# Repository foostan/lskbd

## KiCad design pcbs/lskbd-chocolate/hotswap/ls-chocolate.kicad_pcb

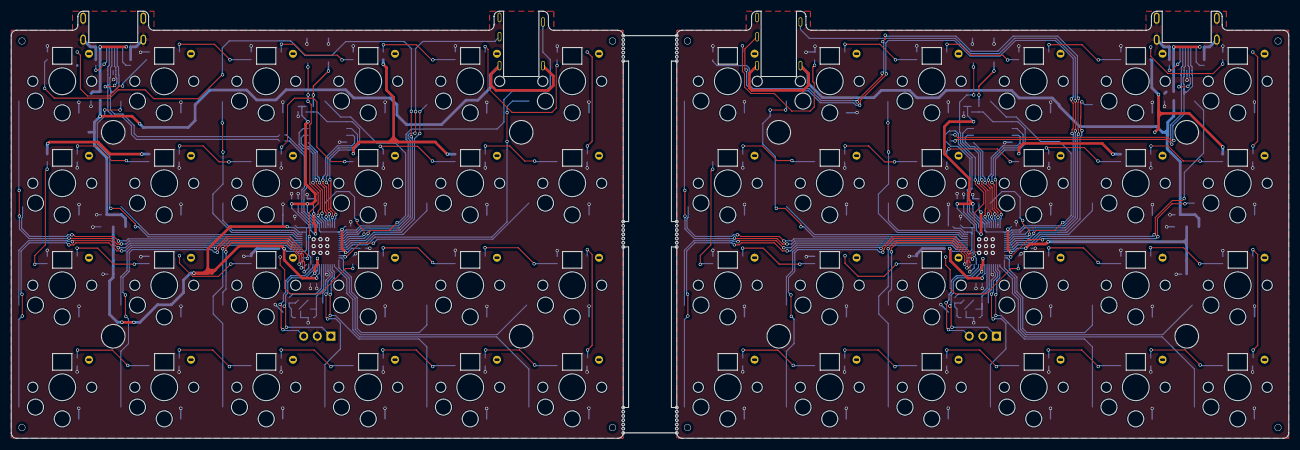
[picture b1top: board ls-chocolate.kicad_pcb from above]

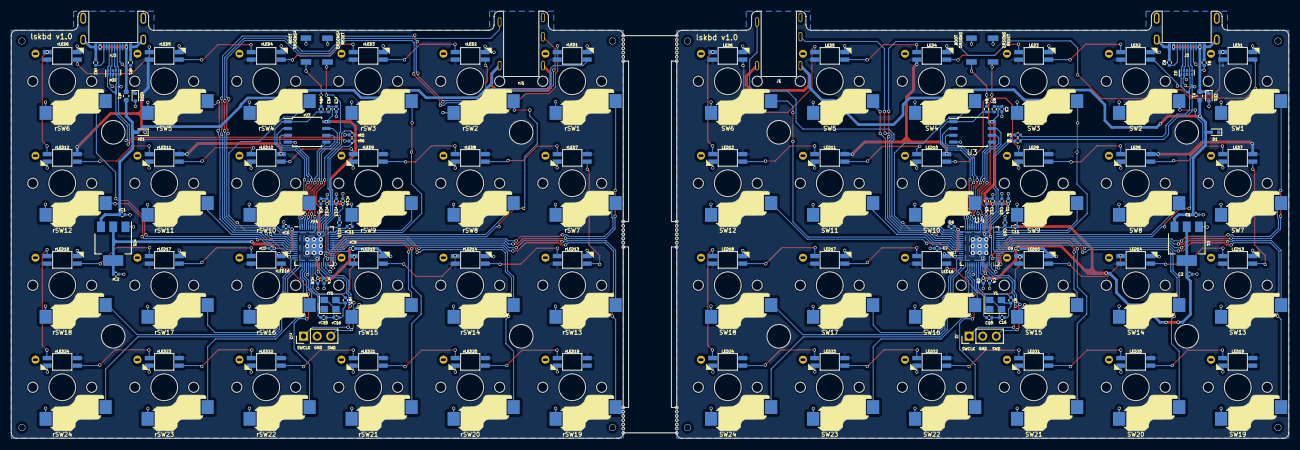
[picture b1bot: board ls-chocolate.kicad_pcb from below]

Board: 2 copper layers, 238.6 x 79.8 mm, 174 parts (168 on the bottom side), 150 nets.

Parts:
BT1, BT2, BT3: Breakaway Tabs; Breakaway_Tabs
C1, C2: 10u; C_0402_1005Metric
C3, C13, C14: 1u; C_0402_1005Metric
C4, C5, C6, C7, C8, C9, C10, C11, C12: 100n; C_0402_1005Metric
C15, C16: 27p; C_0402_1005Metric
D1: 1N4148WT; D_SOD-523
F1: BSMD0603-050-12V; Fuse_0603_1608Metric
J1: ST-0277D00-052-142
J2: Conn_01x03; PinHeader_1x03_P2.54mm_Vertical
J3: TYPE-C-31-M-13C
LED1, LED2, LED3, LED4, LED5, LED6, LED7, LED8, LED9, LED10, LED11, LED12, LED13, LED14, LED15, LED16, LED17, LED18, LED19, LED20, LED21, LED22, LED23, LED24: YS-SK6812MINI-E
R1, R2: 5.1k; R_0402_1005Metric
R3: 10k; R_0402_1005Metric
R4, R7: 1k; R_0402_1005Metric
R5, R6: 27; R_0402_1005Metric
SMDSW1, SMDSW2: TS-1088R-02026
SW1, SW2, SW3, SW4, SW5, SW6, SW7, SW8, SW9, SW10, SW11, SW12, SW13, SW14, SW15, SW16, SW17, SW18, SW19, SW20, SW21, SW22, SW23, SW24: SW_Push; keyswitch_choc12_hotswap_1u
U1: NCP1117LPST33T3G; SOT-223-3_TabPin2
U2: TPD4E05U06DQAR; USON-10_2.5x1.0mm_P0.5mm
U3: W25Q128JVSIQ; SOIC-8_5.23x5.23mm_P1.27mm
U4: RP2040; QFN-56-1EP_7x7mm_P0.4mm_EP3.2x3.2mm
Y1: 12MHz 18pF; Crystal_SMD_3225-4Pin_3.2x2.5mm
ZD1: ESD5Z5V0C; D_SOD-523
rBT1, rBT2, rBT3: Breakaway Tabs; Breakaway_Tabs
rC1, rC2: 10u; C_0402_1005Metric
rC3, rC13, rC14: 1u; C_0402_1005Metric
rC4, rC5, rC6, rC7, rC8, rC9, rC10, rC11, rC12: 100n; C_0402_1005Metric
rC15, rC16: 27p; C_0402_1005Metric
rD1: 1N4148WT; D_SOD-523
rF1: BSMD0603-050-12V; Fuse_0603_1608Metric
rJ1: ST-0277D00-052-142
rJ2: Conn_01x03; PinHeader_1x03_P2.54mm_Vertical
rJ3: TYPE-C-31-M-13C
rLED1, rLED2, rLED3, rLED4, rLED5, rLED6, rLED7, rLED8, rLED9, rLED10, rLED11, rLED12, rLED13, rLED14, rLED15, rLED16, rLED17, rLED18, rLED19, rLED20, rLED21, rLED22, rLED23, rLED24: YS-SK6812MINI-E
rR1, rR2: 5.1k; R_0402_1005Metric
rR3: 10k; R_0402_1005Metric
rR4, rR7: 1k; R_0402_1005Metric
rR5, rR6: 27; R_0402_1005Metric
rSMDSW1, rSMDSW2: TS-1088R-02026
rSW1, rSW2, rSW3, rSW4, rSW5, rSW6, rSW7, rSW8, rSW9, rSW10, rSW11, rSW12, rSW13, rSW14, rSW15, rSW16, rSW17, rSW18, rSW19, rSW20, rSW21, rSW22, rSW23, rSW24: SW_Push; keyswitch_choc12_hotswap_1u
rU1: NCP1117LPST33T3G; SOT-223-3_TabPin2
rU2: TPD4E05U06DQAR; USON-10_2.5x1.0mm_P0.5mm
rU3: W25Q128JVSIQ; SOIC-8_5.23x5.23mm_P1.27mm
rU4: RP2040; QFN-56-1EP_7x7mm_P0.4mm_EP3.2x3.2mm
rY1: 12MHz 18pF; Crystal_SMD_3225-4Pin_3.2x2.5mm
rZD1: ESD5Z5V0C; D_SOD-523

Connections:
+1V1: C4.1, C5.1, C13.1, U4.23 (DVDD), U4.45 (VREG_VOUT), U4.50 (DVDD)
+1V1R: rC4.1, rC5.1, rC13.1, rU4.23 (DVDD), rU4.45 (VREG_VOUT), rU4.50 (DVDD)
+3V3: C2.1, C3.1, C6.1, C7.1, C8.1, C9.1, C10.1, C11.1, C12.1, C14.1, R3.2, U1.2 (VO), U3.8 (VCC), U4.1 (IOVDD), U4.10 (IOVDD), U4.22 (IOVDD), U4.32 (GPIO21), U4.33 (IOVDD), U4.42 (IOVDD), U4.43 (ADC_AVDD), U4.44 (VREG_IN), U4.48 (USB_VDD), U4.49 (IOVDD)
+3V3R: rC2.1, rC3.1, rC6.1, rC7.1, rC8.1, rC9.1, rC10.1, rC11.1, rC12.1, rC14.1, rR3.2, rU1.2 (VO), rU3.8 (VCC), rU4.1 (IOVDD), rU4.10 (IOVDD), rU4.22 (IOVDD), rU4.33 (IOVDD), rU4.42 (IOVDD), rU4.43 (ADC_AVDD), rU4.44 (VREG_IN), rU4.48 (USB_VDD), rU4.49 (IOVDD)
+5V: C1.1, D1.2 (A), F1.2, J1.T, U1.3 (VI)
+5VR: rC1.1, rD1.2 (A), rF1.2, rJ1.T, rU1.3 (VI)
/left/D+: J3.A6 (D+), J3.B6 (D+), R5.1, U2.1 (D1+), U2.4 (D2+), U2.7 (NC), U2.10 (NC)
/left/D-: J3.A7 (D-), J3.B7 (D-), R6.2, U2.2 (D1-), U2.5 (D2-), U2.6 (NC), U2.9 (NC)
/left/KEY1: SW1.1, U4.36 (GPIO24)
/left/KEY2: SW2.1, U4.38 (GPIO26_ADC0)
/left/KEY3: SW3.1, U4.40 (GPIO28_ADC2)
/left/KEY4: SW4.1, U4.6 (GPIO4)
/left/KEY5: SW5.1, U4.7 (GPIO5)
/left/KEY6: SW6.1, U4.9 (GPIO7)
/left/KEY7: SW7.1, U4.37 (GPIO25)
/left/KEY8: SW8.1, U4.39 (GPIO27_ADC1)
/left/KEY9: SW9.1, U4.41 (GPIO29_ADC3)
/left/KEY10: SW10.1, U4.5 (GPIO3)
/left/KEY11: SW11.1, U4.8 (GPIO6)
/left/KEY12: SW12.1, U4.12 (GPIO9)
/left/KEY13: SW13.1, U4.35 (GPIO23)
/left/KEY14: SW14.1, U4.30 (GPIO19)
/left/KEY15: SW15.1, U4.29 (GPIO18)
/left/KEY16: SW16.1, U4.18 (GPIO15)
/left/KEY17: SW17.1, U4.13 (GPIO10)
/left/KEY18: SW18.1, U4.14 (GPIO11)
/left/KEY19: SW19.1, U4.34 (GPIO22)
/left/KEY20: SW20.1, U4.27 (GPIO16)
/left/KEY21: SW21.1, U4.28 (GPIO17)
/left/KEY22: SW22.1, U4.17 (GPIO14)
/left/KEY23: SW23.1, U4.16 (GPIO13)
/left/KEY24: SW24.1, U4.15 (GPIO12)
/left/LED: LED1.4 (DIN), U4.4 (GPIO2)
/left/QSPI_SCLK: U3.6 (CLK), U4.52 (QSPI_SCLK)
/left/QSPI_SD0: U3.5 (DI(IO0)), U4.53 (QSPI_SD0)
/left/QSPI_SD1: U3.2 (DO(IO1)), U4.55 (QSPI_SD1)
/left/QSPI_SD2: U3.3 (IO2), U4.54 (QSPI_SD2)
/left/QSPI_SD3: U3.7 (IO3), U4.51 (QSPI_SD3)
/left/QSPI_SS: R3.1, R4.1, U3.1 (~CS), U4.56 (QSPI_SS)
/left/RX: J1.R1, U4.3 (GPIO1)
/left/SWCLK: J2.1, U4.24 (SWCLK)
/left/SWD: J2.3, U4.25 (SWD)
/left/TX: J1.R2, U4.2 (GPIO0)
/right/D+: rJ3.A6 (D+), rJ3.B6 (D+), rR5.1, rU2.1 (D1+), rU2.4 (D2+), rU2.7 (NC), rU2.10 (NC)
/right/D-: rJ3.A7 (D-), rJ3.B7 (D-), rR6.2, rU2.2 (D1-), rU2.5 (D2-), rU2.6 (NC), rU2.9 (NC)
/right/KEY1: rSW1.1, rU4.36 (GPIO24)
/right/KEY2: rSW2.1, rU4.38 (GPIO26_ADC0)
/right/KEY3: rSW3.1, rU4.40 (GPIO28_ADC2)
/right/KEY4: rSW4.1, rU4.6 (GPIO4)
/right/KEY5: rSW5.1, rU4.7 (GPIO5)
/right/KEY6: rSW6.1, rU4.9 (GPIO7)
/right/KEY7: rSW7.1, rU4.37 (GPIO25)
/right/KEY8: rSW8.1, rU4.39 (GPIO27_ADC1)
/right/KEY9: rSW9.1, rU4.41 (GPIO29_ADC3)
/right/KEY10: rSW10.1, rU4.5 (GPIO3)
/right/KEY11: rSW11.1, rU4.8 (GPIO6)
/right/KEY12: rSW12.1, rU4.12 (GPIO9)
/right/KEY13: rSW13.1, rU4.35 (GPIO23)
/right/KEY14: rSW14.1, rU4.30 (GPIO19)
/right/KEY15: rSW15.1, rU4.29 (GPIO18)
/right/KEY16: rSW16.1, rU4.18 (GPIO15)
/right/KEY17: rSW17.1, rU4.13 (GPIO10)
/right/KEY18: rSW18.1, rU4.14 (GPIO11)
/right/KEY19: rSW19.1, rU4.34 (GPIO22)
/right/KEY20: rSW20.1, rU4.27 (GPIO16)
/right/KEY21: rSW21.1, rU4.28 (GPIO17)
/right/KEY22: rSW22.1, rU4.17 (GPIO14)
/right/KEY23: rSW23.1, rU4.16 (GPIO13)
/right/KEY24: rSW24.1, rU4.15 (GPIO12)
/right/LED: rLED1.4 (DIN), rU4.4 (GPIO2)
/right/QSPI_SCLK: rU3.6 (CLK), rU4.52 (QSPI_SCLK)
/right/QSPI_SD0: rU3.5 (DI(IO0)), rU4.53 (QSPI_SD0)
/right/QSPI_SD1: rU3.2 (DO(IO1)), rU4.55 (QSPI_SD1)
/right/QSPI_SD2: rU3.3 (IO2), rU4.54 (QSPI_SD2)
/right/QSPI_SD3: rU3.7 (IO3), rU4.51 (QSPI_SD3)
/right/QSPI_SS: rR3.1, rR4.1, rU3.1 (~CS), rU4.56 (QSPI_SS)
/right/RX: rJ1.R2, rU4.3 (GPIO1)
/right/SWCLK: rJ2.1, rU4.24 (SWCLK)
/right/SWD: rJ2.3, rU4.25 (SWD)
/right/TX: rJ1.R1, rU4.2 (GPIO0)
GND: C1.2, C2.2, C3.2, C4.2, C5.2, C6.2, C7.2, C8.2, C9.2, C10.2, C11.2, C12.2, C13.2, C14.2, C15.2, C16.2, J1.S, J2.2, J3.A1 (GND), J3.A12 (GND), J3.B1 (GND), J3.B12 (GND), J3.S1 (SHIELD), LED1.3 (VSS), LED2.3 (VSS), LED3.3 (VSS), LED4.3 (VSS), LED5.3 (VSS), LED6.3 (VSS), LED7.3 (VSS), LED8.3 (VSS), LED9.3 (VSS), LED10.3 (VSS), LED11.3 (VSS), LED12.3 (VSS), LED13.3 (VSS), LED14.3 (VSS), LED15.3 (VSS), LED16.3 (VSS), LED17.3 (VSS), LED18.3 (VSS), LED19.3 (VSS), LED20.3 (VSS), LED21.3 (VSS), LED22.3 (VSS), LED23.3 (VSS), LED24.3 (VSS), R1.1, R2.1, SMDSW1.1, SMDSW2.1, SW1.2, SW2.2, SW3.2, SW4.2, SW5.2, SW6.2, SW7.2, SW8.2, SW9.2, SW10.2, SW11.2, SW12.2, SW13.2, SW14.2, SW15.2, SW16.2, SW17.2, SW18.2, SW19.2, SW20.2, SW21.2, SW22.2, SW23.2, SW24.2, U1.1 (GND), U2.3 (GND), U2.8 (GND), U3.4 (GND), U4.19 (TESTEN), U4.57 (GND), Y1.2, Y1.4, ZD1.2 (A)
GNDR: rC1.2, rC2.2, rC3.2, rC4.2, rC5.2, rC6.2, rC7.2, rC8.2, rC9.2, rC10.2, rC11.2, rC12.2, rC13.2, rC14.2, rC15.2, rC16.2, rJ1.S, rJ2.2, rJ3.A1 (GND), rJ3.A12 (GND), rJ3.B1 (GND), rJ3.B12 (GND), rJ3.S1 (SHIELD), rLED1.3 (VSS), rLED2.3 (VSS), rLED3.3 (VSS), rLED4.3 (VSS), rLED5.3 (VSS), rLED6.3 (VSS), rLED7.3 (VSS), rLED8.3 (VSS), rLED9.3 (VSS), rLED10.3 (VSS), rLED11.3 (VSS), rLED12.3 (VSS), rLED13.3 (VSS), rLED14.3 (VSS), rLED15.3 (VSS), rLED16.3 (VSS), rLED17.3 (VSS), rLED18.3 (VSS), rLED19.3 (VSS), rLED20.3 (VSS), rLED21.3 (VSS), rLED22.3 (VSS), rLED23.3 (VSS), rLED24.3 (VSS), rR1.1, rR2.1, rSMDSW1.1, rSMDSW2.1, rSW1.2, rSW2.2, rSW3.2, rSW4.2, rSW5.2, rSW6.2, rSW7.2, rSW8.2, rSW9.2, rSW10.2, rSW11.2, rSW12.2, rSW13.2, rSW14.2, rSW15.2, rSW16.2, rSW17.2, rSW18.2, rSW19.2, rSW20.2, rSW21.2, rSW22.2, rSW23.2, rSW24.2, rU1.1 (GND), rU2.3 (GND), rU2.8 (GND), rU3.4 (GND), rU4.19 (TESTEN), rU4.32 (GPIO21), rU4.57 (GND), rY1.2, rY1.4, rZD1.2 (A)
unnamed: C16.1, R7.1, Y1.3
unnamed: D1.1 (K), LED1.1 (VDD), LED2.1 (VDD), LED3.1 (VDD), LED4.1 (VDD), LED5.1 (VDD), LED6.1 (VDD), LED7.1 (VDD), LED8.1 (VDD), LED9.1 (VDD), LED10.1 (VDD), LED11.1 (VDD), LED12.1 (VDD), LED13.1 (VDD), LED14.1 (VDD), LED15.1 (VDD), LED16.1 (VDD), LED17.1 (VDD), LED18.1 (VDD), LED19.1 (VDD), LED20.1 (VDD), LED21.1 (VDD), LED22.1 (VDD), LED23.1 (VDD), LED24.1 (VDD)
unnamed: J3.A5 (CC1), R1.2
unnamed: J3.B5 (CC2), R2.2
unnamed: LED1.2 (DOUT), LED2.4 (DIN)
unnamed: LED2.2 (DOUT), LED3.4 (DIN)
unnamed: LED3.2 (DOUT), LED4.4 (DIN)
unnamed: LED4.2 (DOUT), LED5.4 (DIN)
unnamed: LED5.2 (DOUT), LED6.4 (DIN)
unnamed: LED7.4 (DIN), LED8.2 (DOUT)
unnamed: LED8.4 (DIN), LED9.2 (DOUT)
unnamed: LED10.4 (DIN), LED11.2 (DOUT)
unnamed: LED9.4 (DIN), LED10.2 (DOUT)
unnamed: LED11.4 (DIN), LED12.2 (DOUT)
unnamed: LED6.2 (DOUT), LED12.4 (DIN)
unnamed: LED7.2 (DOUT), LED13.4 (DIN)
unnamed: LED13.2 (DOUT), LED14.4 (DIN)
unnamed: LED14.2 (DOUT), LED15.4 (DIN)
unnamed: LED15.2 (DOUT), LED16.4 (DIN)
unnamed: LED16.2 (DOUT), LED17.4 (DIN)
unnamed: LED17.2 (DOUT), LED18.4 (DIN)
unnamed: LED18.2 (DOUT), LED24.4 (DIN)
unnamed: LED19.4 (DIN), LED20.2 (DOUT)
unnamed: LED20.4 (DIN), LED21.2 (DOUT)
unnamed: LED21.4 (DIN), LED22.2 (DOUT)
unnamed: LED22.4 (DIN), LED23.2 (DOUT)
unnamed: LED23.4 (DIN), LED24.2 (DOUT)
unnamed: R4.2, SMDSW1.2
unnamed: SMDSW2.2, U4.26 (RUN)
unnamed: R6.1, U4.46 (USB_DM)
unnamed: R5.2, U4.47 (USB_DP)
unnamed: C15.1, U4.20 (XIN), Y1.1
unnamed: R7.2, U4.21 (XOUT)
unnamed: rC16.1, rR7.1, rY1.3
unnamed: rD1.1 (K), rLED1.1 (VDD), rLED2.1 (VDD), rLED3.1 (VDD), rLED4.1 (VDD), rLED5.1 (VDD), rLED6.1 (VDD), rLED7.1 (VDD), rLED8.1 (VDD), rLED9.1 (VDD), rLED10.1 (VDD), rLED11.1 (VDD), rLED12.1 (VDD), rLED13.1 (VDD), rLED14.1 (VDD), rLED15.1 (VDD), rLED16.1 (VDD), rLED17.1 (VDD), rLED18.1 (VDD), rLED19.1 (VDD), rLED20.1 (VDD), rLED21.1 (VDD), rLED22.1 (VDD), rLED23.1 (VDD), rLED24.1 (VDD)
unnamed: rJ3.A5 (CC1), rR1.2
unnamed: rJ3.B5 (CC2), rR2.2
unnamed: rLED1.2 (DOUT), rLED2.4 (DIN)
unnamed: rLED2.2 (DOUT), rLED3.4 (DIN)
unnamed: rLED3.2 (DOUT), rLED4.4 (DIN)
unnamed: rLED4.2 (DOUT), rLED5.4 (DIN)
unnamed: rLED5.2 (DOUT), rLED6.4 (DIN)
unnamed: rLED7.4 (DIN), rLED8.2 (DOUT)
unnamed: rLED8.4 (DIN), rLED9.2 (DOUT)
unnamed: rLED10.4 (DIN), rLED11.2 (DOUT)
unnamed: rLED9.4 (DIN), rLED10.2 (DOUT)
unnamed: rLED11.4 (DIN), rLED12.2 (DOUT)
unnamed: rLED6.2 (DOUT), rLED12.4 (DIN)
unnamed: rLED7.2 (DOUT), rLED13.4 (DIN)
unnamed: rLED13.2 (DOUT), rLED14.4 (DIN)
unnamed: rLED14.2 (DOUT), rLED15.4 (DIN)
unnamed: rLED15.2 (DOUT), rLED16.4 (DIN)
unnamed: rLED16.2 (DOUT), rLED17.4 (DIN)
unnamed: rLED17.2 (DOUT), rLED18.4 (DIN)
unnamed: rLED18.2 (DOUT), rLED24.4 (DIN)
unnamed: rLED19.4 (DIN), rLED20.2 (DOUT)
unnamed: rLED20.4 (DIN), rLED21.2 (DOUT)
unnamed: rLED21.4 (DIN), rLED22.2 (DOUT)
unnamed: rLED22.4 (DIN), rLED23.2 (DOUT)
unnamed: rLED23.4 (DIN), rLED24.2 (DOUT)
unnamed: rR4.2, rSMDSW1.2
unnamed: rSMDSW2.2, rU4.26 (RUN)
unnamed: rR6.1, rU4.46 (USB_DM)
unnamed: rR5.2, rU4.47 (USB_DP)
unnamed: rC15.1, rU4.20 (XIN), rY1.1
unnamed: rR7.2, rU4.21 (XOUT)
VBUS: F1.1, J3.A4 (VBUS), J3.A9 (VBUS), J3.B4 (VBUS), J3.B9 (VBUS), ZD1.1 (K)
VBUSR: rF1.1, rJ3.A4 (VBUS), rJ3.A9 (VBUS), rJ3.B4 (VBUS), rJ3.B9 (VBUS), rZD1.1 (K)

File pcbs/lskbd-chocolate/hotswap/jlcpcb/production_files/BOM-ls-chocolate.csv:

Comment,Designator,Footprint,LCSC
W25Q128JVSIQ,"U3,rU3",SOIC-8_5.23x5.23mm_P1.27mm,C113767
1k,"R4,R7,rR4,rR7",R_0402_1005Metric,C11702
TPD4E05U06DQAR,"U2,rU2",USON-10_2.5x1.0mm_P0.5mm,C138714
NCP1117LPST33T3G,"U1,rU1",SOT-223-3_TabPin2,C146799
100n,"C10,C11,C12,C4,C5,C6,C7,C8,C9,rC10,rC11,rC12,rC4,rC5,rC6,rC7,rC8,rC9",C_0402_1005Metric,C1525
10u,"C1,C2,rC1,rC2",C_0402_1005Metric,C15525
27p,"C15,C16,rC15,rC16",C_0402_1005Metric,C1557
RP2040,"U4,rU4",QFN-56-1EP_7x7mm_P0.4mm_EP3.2x3.2mm,C2040
1N4148WT,"D1,rD1",D_SOD-523,C232841
10k,"R3,rR3",R_0402_1005Metric,C25744
5.1k,"R1,R2,rR1,rR2",R_0402_1005Metric,C25905
ST-0277D00-052-142,"J1,rJ1",ST-0277D00-052-142,C2837093
BSMD0603-050-12V,"F1,rF1",Fuse_0603_1608Metric,C2844464
TYPE-C-31-M-13C,"J3,rJ3",TYPE-C-31-M-13C,C2848620
ESD5Z5V0C,"ZD1,rZD1",D_SOD-523,C2901325
27,"R5,R6,rR5,rR6",R_0402_1005Metric,C2909343
TS-1088R-02026,"SMDSW1,SMDSW2,rSMDSW1,rSMDSW2",TS-1088R-02026,C455280
YS-SK6812MINI-E,"LED1,LED10,LED11,LED12,LED13,LED14,LED15,LED16,LED17,LED18,LED19,LED2,LED20,LED21,LED22,LED23,LED24,LED3,LED4,LED5,LED6,LED7,LED8,LED9,rLED1,rLED10,rLED11,rLED12,rLED13,rLED14,rLED15,rLED16,rLED17,rLED18,rLED19,rLED2,rLED20,rLED21,rLED22,rLED23,rLED24,rLED3,rLED4,rLED5,rLED6,rLED7,rLED8,rLED9",YS-SK6812MINI-E,C5149201
1u,"C13,C14,C3,rC13,rC14,rC3",C_0402_1005Metric,C52923
SW_Push,"SW1,SW10,SW11,SW12,SW13,SW14,SW15,SW16,SW17,SW18,SW19,SW2,SW20,SW21,SW22,SW23,SW24,SW3,SW4,SW5,SW6,SW7,SW8,SW9,rSW1,rSW10,rSW11,rSW12,rSW13,rSW14,rSW15,rSW16,rSW17,rSW18,rSW19,rSW2,rSW20,rSW21,rSW22,rSW23,rSW24,rSW3,rSW4,rSW5,rSW6,rSW7,rSW8,rSW9",keyswitch_choc12_hotswap_1u,C5333465
12MHz 18pF,"Y1,rY1",Crystal_SMD_3225-4Pin_3.2x2.5mm,C91749

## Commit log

2018-04-10 Add plate data
2018-05-22 Add a bottom plate
2018-05-22 Output pdf and dxf
2018-05-22 Add buildguid_jp file
2018-05-23 Add LICENSE
2024-01-26 Add pcb files
2024-01-26 Squashed 'pcbs/common/kbd/' content from commit 43da0ca
    git-subtree-dir: pcbs/common/kbd
    git-subtree-split: 43da0ca3d5e3e0a628e7d64e4fce58097fee60bb
2024-01-26 Squashed 'pcbs/common/kbd/' changes from 43da0ca..1203fd9
    1203fd9 Update choc silk
    git-subtree-dir: pcbs/common/kbd
    git-subtree-split: 1203fd98feca15ec3eaaca5674fcea1d56e84fb0
2024-01-26 Set factory files
2024-01-28 Update case files
2024-01-28 Update pcb
2024-03-01 Add buildguide
2024-03-01 Update case data
